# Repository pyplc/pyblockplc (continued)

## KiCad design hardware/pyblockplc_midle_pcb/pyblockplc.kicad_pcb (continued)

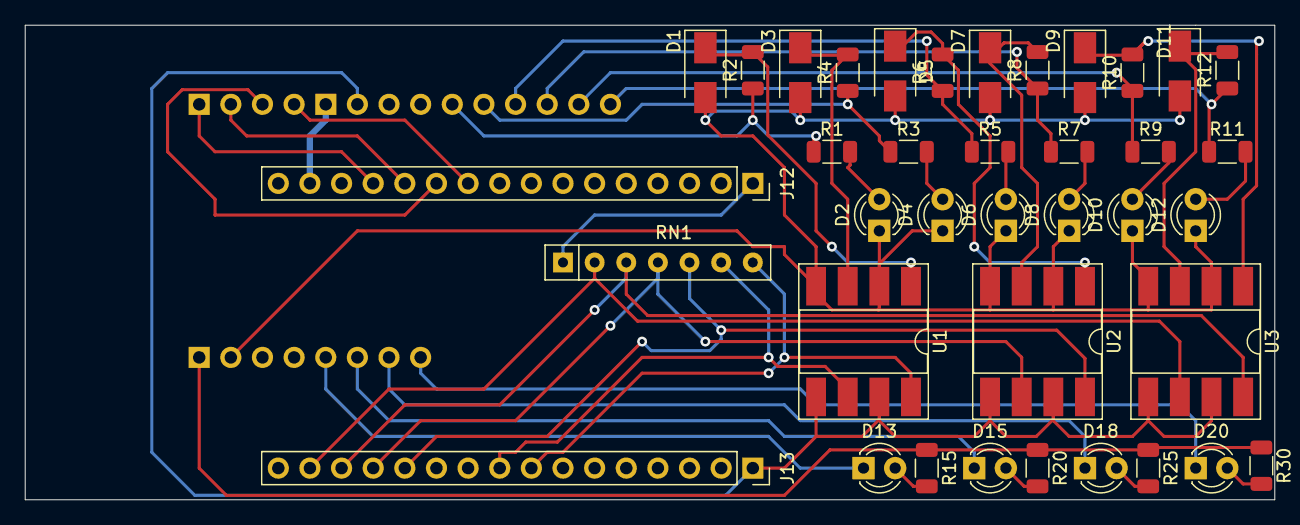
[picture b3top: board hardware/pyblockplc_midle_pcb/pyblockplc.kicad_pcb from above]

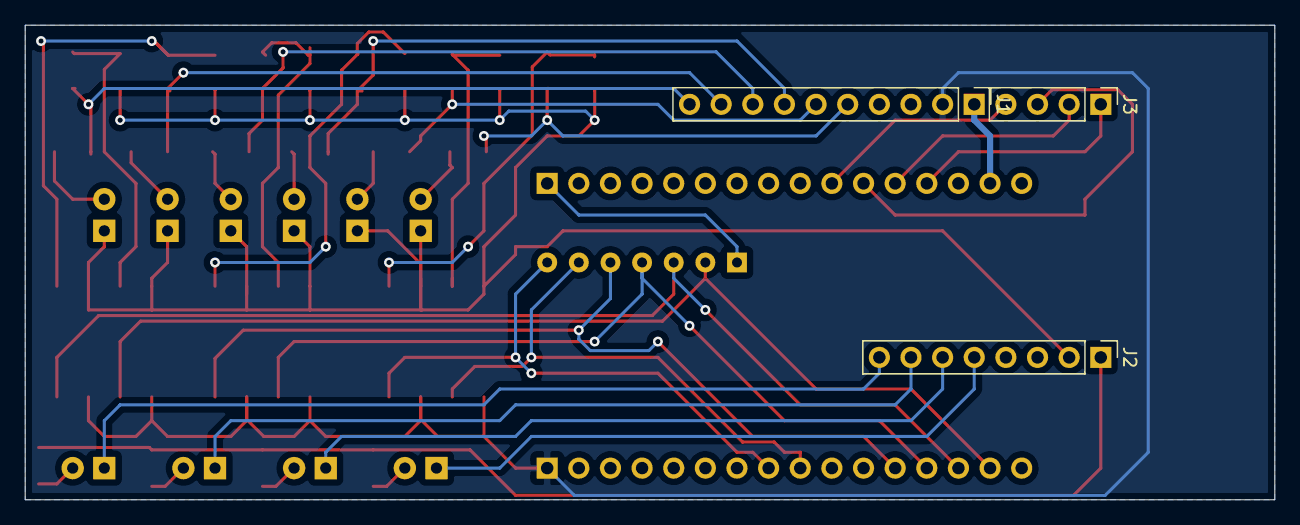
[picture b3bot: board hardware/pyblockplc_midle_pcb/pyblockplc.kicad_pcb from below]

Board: 2 copper layers, 100.3 x 38.1 mm, 41 parts (3 on the bottom side), 41 nets.
